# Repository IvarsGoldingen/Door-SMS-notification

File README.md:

# Door SMS notification

A device that sends an SMS notification when a door is opened. Setup on Atmega Atmel 328P arduino prototyping board together with SIM900 board. The schematic, part layout on the prototyping board and code included in this repository.

## Functions

* SMS notification of door opened event;
* 3 modes: send always, never send, send depending on time;
* Uses RTC on the SIM900 module to evaluate if SMS needs to be sent or not if sending depending on time enabled;
* Sends notification if battery gets low;
* Indication lights.

## Photos

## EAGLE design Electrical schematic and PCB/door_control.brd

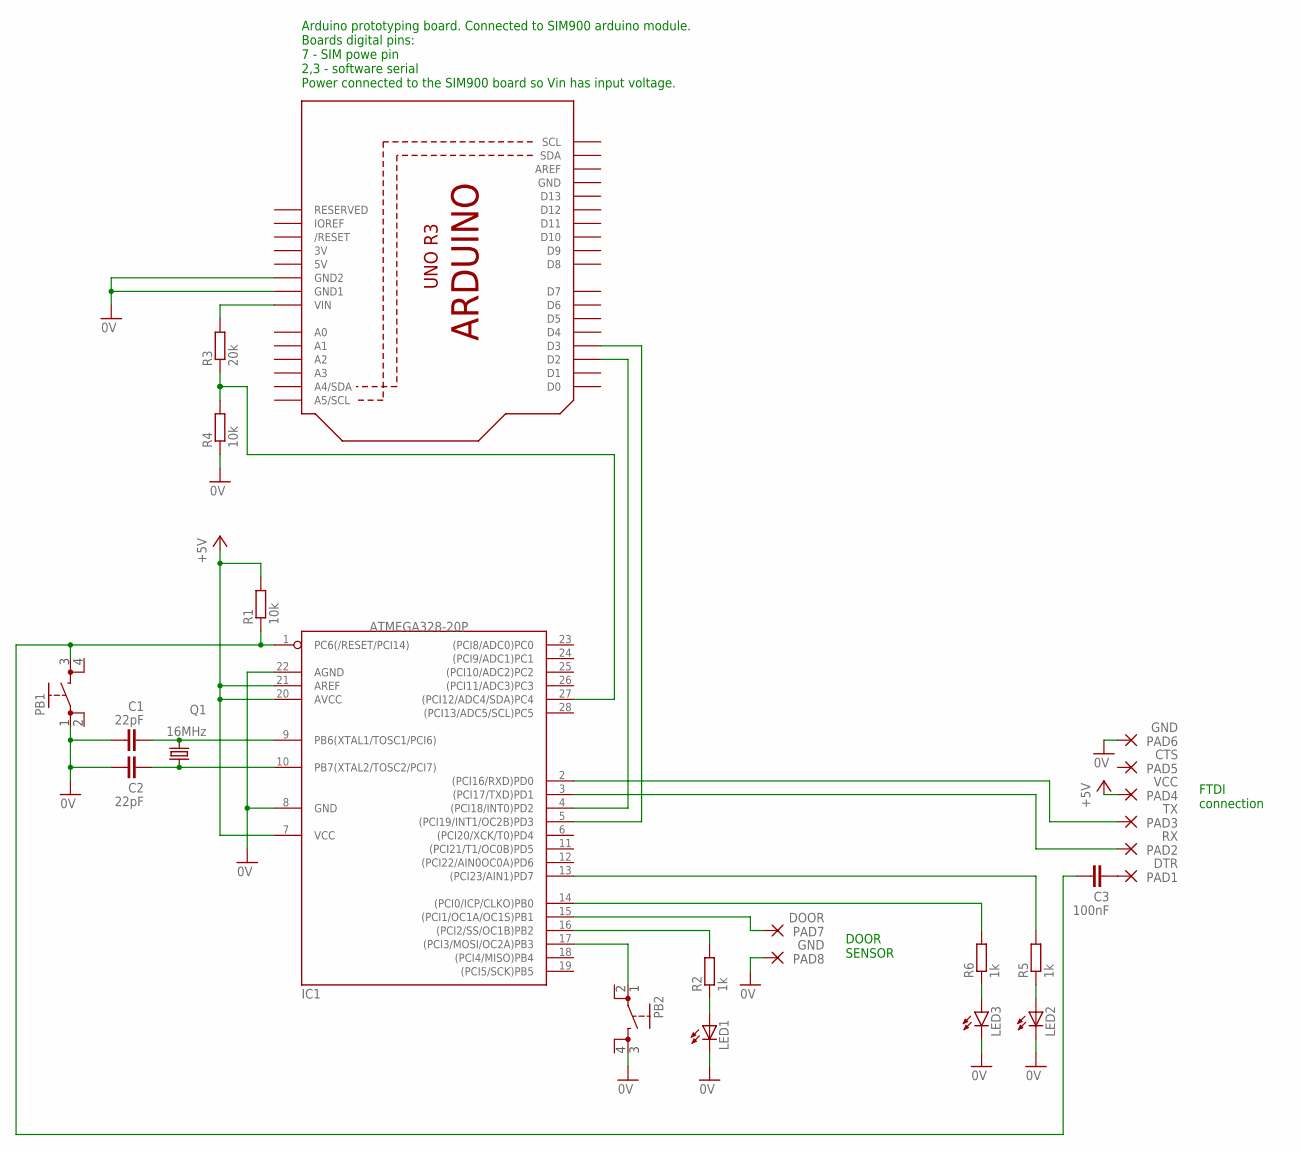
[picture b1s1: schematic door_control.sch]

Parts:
C1, C2: 22pF; C5B2.5
C3: 100nF; C10B4
IC1: ATMEGA328-20P; DIL28-3
LED1, LED2: LED_ELD260; LED_LD260
LED3: LED5MM
PAD1: DTR; 1,6/0,9
PAD2: RX; 1,6/0,9
PAD3: TX; 1,6/0,9
PAD4: VCC; 1,6/0,9
PAD5: CTS; 1,6/0,9
PAD6, PAD8: GND; 1,6/0,9
PAD7: DOOR; 1,6/0,9
PB1, PB2: 4P_BUTTONTH; 4P_BUTTON
Q1: 16MHz; HC49/S
R1: 10k; 0207/10
R2, R5, R6: 1k; 0204/5
R3: 20k; 0204/5
R4: 10k; 0204/5
U1: ARDUINOR3-DIMENSION; ARDUINOR3

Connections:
0V: C1.1, C2.1, IC1.8 (GND), IC1.22 (AGND), LED1.K (C), LED2.K (C), LED3.K (C), PAD6.1, PAD8.1, PB1.1, PB2.3, R4.1, U1.GND1, U1.GND2
3V: U1.3V
5V: U1.5V
+5V: IC1.7 (VCC), IC1.20 (AVCC), IC1.21 (AREF), PAD4.1, R1.2
GND: U1.GND
unnamed: C1.2, IC1.9 (PB6(XTAL1/TOSC1/PCI6)), Q1.2
unnamed: C2.2, IC1.10 (PB7(XTAL2/TOSC2/PCI7)), Q1.1
unnamed: C3.1, IC1.1 (PC6(/RESET/PCI14)), PB1.3, R1.1
unnamed: IC1.3 ((PCI17/TXD)PD1), PAD2.1
unnamed: IC1.2 ((PCI16/RXD)PD0), PAD3.1
unnamed: C3.2, PAD1.1
unnamed: IC1.15 ((PCI1/OC1A/OC1S)PB1), PAD7.1
unnamed: LED1.A, R2.1
unnamed: IC1.4 ((PCI18/INT0)PD2), U1.D2
unnamed: IC1.17 ((PCI3/MOSI/OC2A)PB3), PB2.1
unnamed: IC1.5 ((PCI19/INT1/OC2B)PD3), U1.D3
unnamed: IC1.27 ((PCI12/ADC4/SDA)PC4), R3.1, R4.2
unnamed: R3.2, U1.VIN
unnamed: IC1.13 ((PCI23/AIN1)PD7), R5.2
unnamed: LED2.A, R5.1
unnamed: IC1.14 ((PCI0/ICP/CLKO)PB0), R6.2
unnamed: LED3.A, R6.1
unnamed: IC1.16 ((PCI2/SS/OC1B)PB2), R2.2

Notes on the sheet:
FTDI connection
DOOR SENSOR
Arduino prototyping board. Connected to SIM900 arduino module. Boards digital pins: 7 - SIM powe pin 2,3 - software serial Power connected to the SIM900 board so Vin has input voltage.

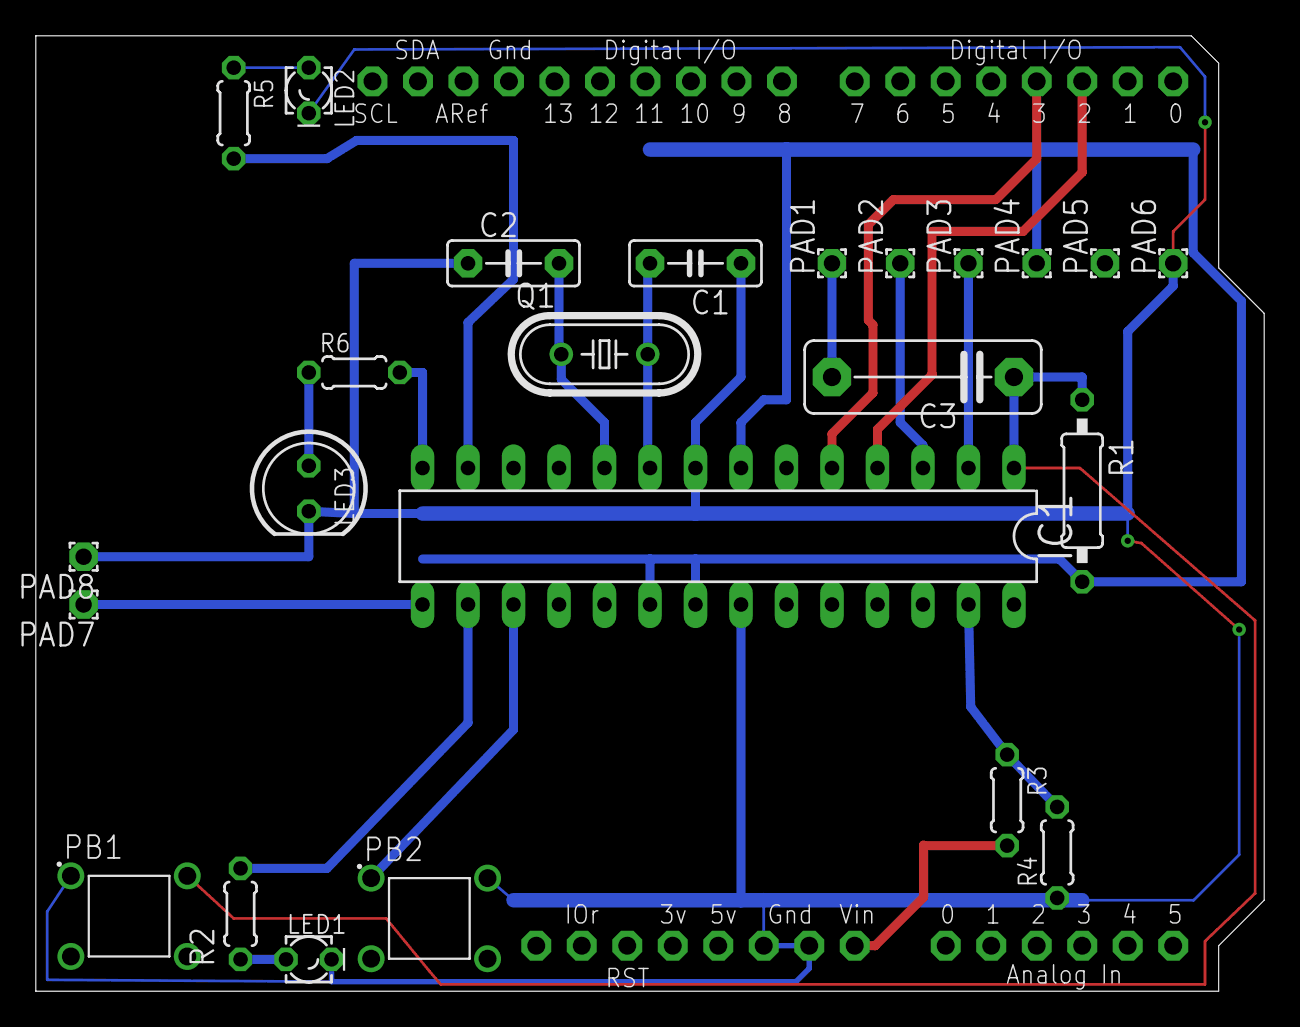
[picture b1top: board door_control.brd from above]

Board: 2 copper layers, 68.6 x 53.3 mm, 25 parts (0 on the bottom side), 20 nets.

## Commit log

2019-03-03 Initial comit
    Initial commit
2019-03-03 Push test
    Push test
2019-03-09 Minor fixes
    Tested with actual devices
2019-03-10 RTC implemented
    Reading and setting RTC has been added.
2019-03-17 Working beta
    First stable version, device sends SMS on door open. Sending depending on time implemented.
    Mode change button implemented.
2019-03-24 Input voltage read
    The device now also sends a SMS message if the input voltage gets too low. For battery protection.
2019-03-31 Schematic added
    Project moved from Arduino UNO to Arduino prototyping board with Atmega328P. Pins in code changed accordingly.
2019-04-11 Update README.md
    Description added
2019-04-11 Update README.md
    Added photo
